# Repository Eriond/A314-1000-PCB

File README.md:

# A314-1000-PCB
A314 board for the A1000's front memory expansion bay

<p>This is the Amiga 1000 version of [the A314](https://github.com/niklasekstrom/a314), designed to fit in the front expansion bay of the iconic computer.<br>
It is built using readily available components and has been designed with the DIY builder in mind (ie. no BGA chips, and reasonably large components with external leads)</p>
<p>It is a 1:1 replacement for the A1050 C= memory expansion, and will provide 256kB of chipRAM regardless if the RPiZ module is present.<br>
The board has room for an optional RTC chip which can provide time and date to the RPiZ via an I2C bus. This bus has also been made available via solderpads and is accessible from both sides of the PCB. It can be useful if you'd like to add other peripherals, like RGB lights or an OLED display for instance.</p>

For more information on how to bring this hardware to life, please check out Niklas repository at [https://github.com/niklasekstrom/a314-1000-gateware](https://github.com/niklasekstrom/a314-1000-gateware)

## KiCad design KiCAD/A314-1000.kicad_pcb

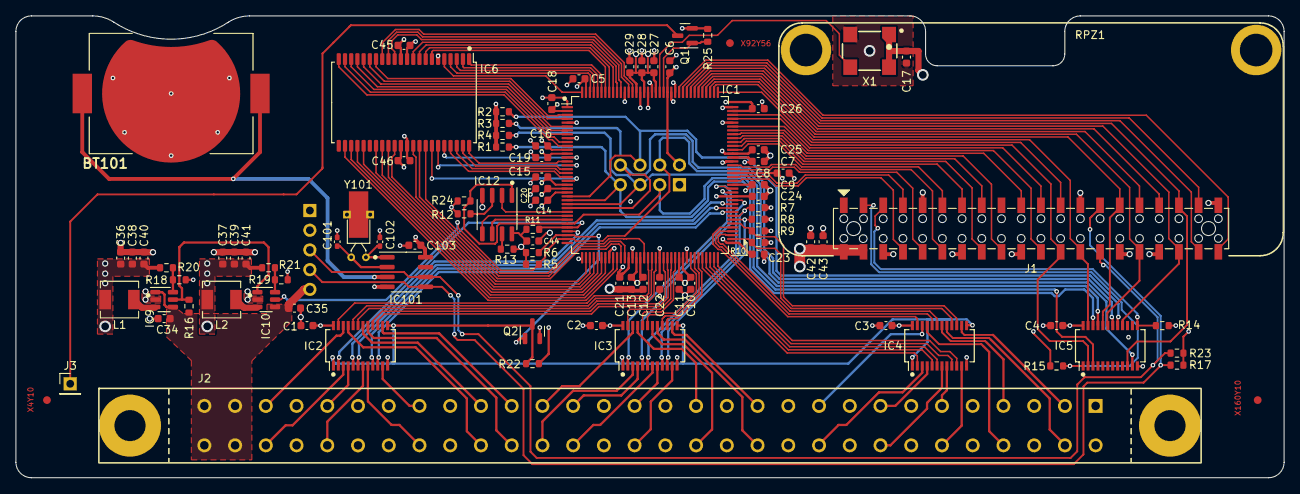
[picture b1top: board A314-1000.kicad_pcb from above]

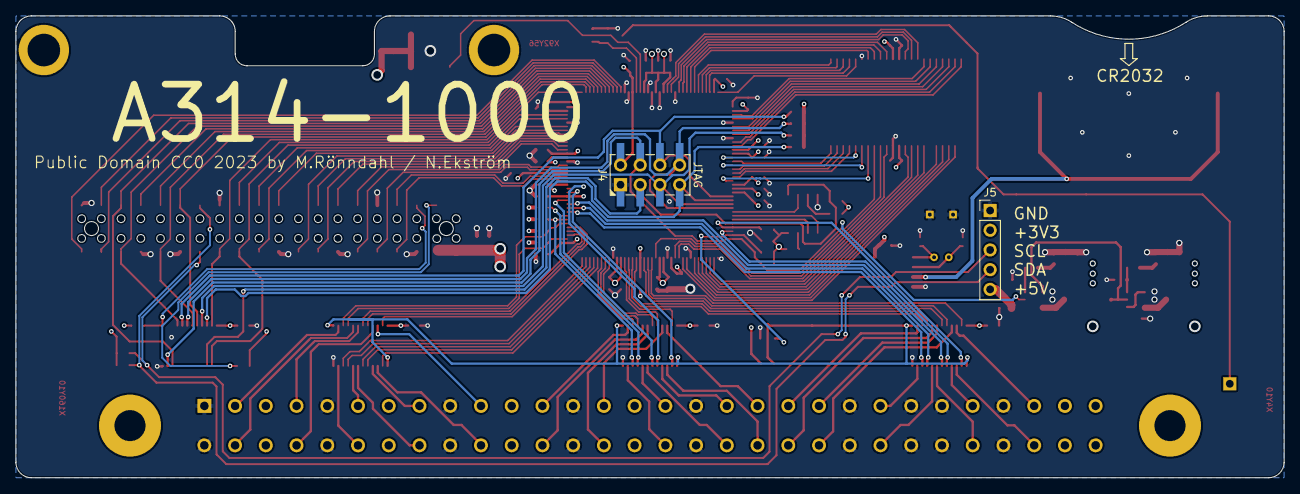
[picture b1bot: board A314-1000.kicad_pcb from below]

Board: 4 copper layers, 163.4 x 59.5 mm, 98 parts (2 on the bottom side), 153 nets.

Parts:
BT101: CR2032; BATHLD001
C1, C2, C3, C4, C5, C6, C7, C8, C9, C10, C11, C12, C13, C14, C15, C16, C17, C18, C19, C20, C21, C22, C23, C24, C25, C26, C27, C28, C29, C44, C45, C46, C103: 100n; C_0603_1608Metric
C34, C35: 4µ7; C_0603_1608Metric
C36, C37, C38, C39, C40, C41, C42, C43: 10µ; C_0603_1608Metric
C101, C102: 8p; C_0402_1005Metric_Pad0.74x0.62mm_HandSolder
FID1, FID2, FID3: Fiducial; Fiducial_1mm_Mask2mm
H1, H2: MountingHole; M2.5_Mount
IC1: T8Q144xx; LQFP-144_20x20mm_P0.5mm
IC2, IC3, IC4, IC5: SN74CBTD3384CPWR; SSOP-24_3.9x8.7mm_P0.635mm
IC6: IS61WV12816EDBLL-10TLI; TSOP-II-44_10.16x18.41mm_P0.8mm
IC9, IC10: TLV62569P; SOT-23-6
IC12: W25Q80DVSN; SOIC-8_3.9x4.9mm_P1.27mm
IC101: PT7C4311WEX; SOIC-8_3.9x4.9mm_P1.27mm
J1: Raspberry_Pi_2_3; LianSheng-FH-00339
J2: 2x30 Card edge conn.; 337-060-52x-804
J3: INT2; PinHeader_1x01_P2.54mm_Vertical
J4: JTAG; PinHeader_2x04_P2.54mm_Vertical_Multi
J5: RASP_I2C; PinHeader_1x05_P2.54mm_Vertical
L1, L2: 2.2uH; L_Sunlord_MWSA0402S
Q1, Q2: 2N7002; SOT-23
R1, R2, R3, R4, R5, R6, R7, R8, R9, R10, R11, R12, R13, R14, R15, R24: 10k; R_0603_1608Metric
R16, R21: 442k; R_0603_1608Metric
R17, R23, R25: 3k9; R_0603_1608Metric
R18, R19, R20: 100k; R_0603_1608Metric
R22: 1k8; R_0603_1608Metric
RPZ1: RPiZ; RPiZ mount
X1: 25MHz; HSO751S
Y101: 32.768kHz; Crystal_DS26_D2.0mm_L6.0mm_Horizontal_1EP_style2

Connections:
+1V2: C18.1, C19.1, C20.1, C21.1, C22.1, C23.1, C24.1, C25.1, C26.1, C27.1, C28.1, C29.1, C36.1, C38.1, C40.1, IC1.2 (VCCA_TL), IC1.13 (VCC), IC1.22 (VCC), IC1.49 (VCC), IC1.57 (VCC), IC1.73 (VCCA_BR), IC1.85 (VCC), IC1.96 (VCC), IC1.107 (VCCA_TR), IC1.125 (VCC), IC1.128 (VCC), IC1.130 (VCC), L1.2, R20.2
+3V3: C5.1, C6.1, C7.1, C8.1, C9.1, C10.1, C11.1, C12.1, C13.1, C14.1, C15.1, C16.1, C17.1, C37.1, C39.1, C41.1, C44.1, C45.1, C46.1, C103.1, IC1.12 (VCCIO1CD), IC1.21 (VCCIO1B), IC1.23 (VCCIO1A), IC1.51 (VCCIO4B), IC1.52 (VCCIO4B), IC1.62 (VCCIO4A), IC1.63 (VCCIO4A), IC1.88 (VCCIO3E), IC1.91 (VCCIO3D), IC1.95 (VCCIO3BC), IC1.122 (VCCIO3A), IC1.143 (VCCIO1E), IC6.11 (VDD), IC6.33 (VDD), IC12.8 (VCC), IC101.8 (V_{cc}), J4.2 (Vcc), J5.2, L2.2, R1.2, R2.2, R3.2, R4.2, R5.2, R6.2, R7.2, R8.2, R9.2, R10.2, R11.2, R12.1, R13.2, R14.2, R15.2, R17.2, R21.2, R22.2, R23.2, R24.2, X1.1 (OE), X1.4 (Vdd)
+5V: C1.1, C2.1, C3.1, C4.1, C34.1, C35.1, C42.1, C43.1, IC2.24 (VCC), IC3.24 (VCC), IC4.24 (VCC), IC5.24 (VCC), IC9.1 (EN), IC9.4 (VIN), IC10.4 (VIN), J1.2 (5V), J1.4 (5V), J2.3, J2.7, J2.11, J2.15, J2.29, J2.30, J2.C, J2.H, J2.HH, J2.JJ, J2.M, J2.S, J5.5, R16.2
/1V2PG: IC9.5 (PG), IC10.1 (EN), R16.1
/3VA_{0}: IC1.55 (GPIOB_RXP00), IC2.20 (2B4)
/3VA_{1}: IC1.58 (GPIOB_RXP02), IC2.16 (2B2)
/3VA_{2}: IC1.86 (GPIOR_133/CDI18), IC3.2 (1B1)
/3VA_{3}: IC1.84 (GPIOR_135/CDI17), IC3.6 (1B3)
/3VA_{4}: IC1.87 (GPIOR_132/CDI19), IC3.5 (1B2)
/3VA_{5}: IC1.60 (GPIOB_RXN03), IC3.23 (2B5)
/3VA_{6}: IC1.59 (GPIOB_RXN02), IC2.15 (2B1)
/3VA_{7}: IC1.56 (GPIOB_RXN00), IC2.19 (2B3)
/3VCASL_{0}: IC1.54 (GPIOB_TXN11), IC2.23 (2B5)
/3VCASL_{1}: IC1.32 (GPIOL_04/CSI), IC2.2 (1B1), R11.1
/3VCASU_{0}: IC1.33 (GPIOL_05/CSO), IC2.5 (1B2)
/3VCASU_{1}: IC1.83 (GPIOR_136/CDI16), IC2.6 (1B3)
/3VD_{0}: IC1.80 (GPIOR_149/CBUS2), IC3.9 (1B4), R7.1
/3VD_{1}: IC1.79 (GPIOR_150/CBUS1), IC3.10 (1B5), R8.1
/3VD_{2}: IC1.65 (GPIOB_RXN07), IC3.19 (2B3)
/3VD_{3}: IC1.61 (GPIOB_RXP03), IC3.20 (2B4)
/3VD_{4}: IC1.67 (GPIOB_RXP10), IC3.15 (2B1)
/3VD_{5}: IC1.66 (GPIOB_RXP07), IC3.16 (2B2)
/3VD_{6}: IC1.68 (GPIOB_RXN10), IC4.2 (1B1)
/3VD_{7}: IC1.77 (GPIOR_154), IC4.23 (2B5)
/3VD_{8}: IC1.69 (GPIOB_RXN12_EXTFB0), IC4.5 (1B2)
/3VD_{9}: IC1.70 (GPIOB_RXP12_EXTFB0), IC4.6 (1B3)
/3VD_{10}: IC1.72 (GPIOB_CLKN0), IC4.10 (1B5)
/3VD_{11}: IC1.71 (GPIOB_CLKP0), IC4.9 (1B4)
/3VD_{12}: IC1.75 (GPIOR_157/PLLIN), IC4.19 (2B3)
/3VD_{13}: IC1.76 (GPIOR_155), IC4.20 (2B4)
/3VD_{14}: IC1.74 (GPIOR_158/~TEST), IC4.16 (2B2), R10.1
/3VD_{15}: IC1.78 (GPIOR_151/CBUS0), IC4.15 (2B1), R9.1
/3VRAS: IC1.81 (GPIOR_139), IC2.10 (1B5)
/3VRRW: IC1.82 (GPIOR_138), IC2.9 (1B4)
/AMA_{0}: IC2.21 (2A4), J2.Y
/AMA_{1}: IC2.17 (2A2), J2.X
/AMA_{2}: IC3.3 (1A1), J2.W
/AMA_{3}: IC3.7 (1A3), J2.V
/AMA_{4}: IC3.4 (1A2), J2.18
/AMA_{5}: IC3.22 (2A5), J2.19
/AMA_{6}: IC2.14 (2A1), J2.20
/AMA_{7}: IC2.18 (2A3), J2.21
/AMCASL_{0}: IC2.22 (2A5), J2.28
/AMCASL_{1}: IC2.3 (1A1), J2.FF
/AMCASU_{0}: IC2.4 (1A2), J2.26
/AMCASU_{1}: IC2.7 (1A3), J2.DD
/AMD_{0}: IC3.8 (1A4), J2.16
/AMD_{1}: IC3.11 (1A5), J2.T
/AMD_{2}: IC3.18 (2A3), J2.R
/AMD_{3}: IC3.21 (2A4), J2.14
/AMD_{4}: IC3.14 (2A1), J2.12
/AMD_{5}: IC3.17 (2A2), J2.N
/AMD_{6}: IC4.3 (1A1), J2.L
/AMD_{7}: IC4.22 (2A5), J2.10
/AMD_{8}: IC4.4 (1A2), J2.8
/AMD_{9}: IC4.7 (1A3), J2.J
/AMD_{10}: IC4.11 (1A5), J2.F
/AMD_{11}: IC4.8 (1A4), J2.6
/AMD_{12}: IC4.18 (2A3), J2.4
/AMD_{13}: IC4.21 (2A4), J2.D
/AMD_{14}: IC4.17 (2A2), J2.B
/AMD_{15}: IC4.14 (2A1), J2.2
/AMRAS: IC2.11 (1A5), J2.23
/AMRRW: IC2.8 (1A4), J2.AA
/A_{0}: IC1.144 (GPIOL_64), IC6.5 (A0)
/A_{1}: IC1.142 (GPIOL_66/CDI12), IC6.4 (A1)
/A_{2}: IC1.141 (GPIOL_65), IC6.3 (A2)
/A_{3}: IC1.140 (GPIOL_67/CDI13), IC6.2 (A3)
/A_{4}: IC1.139 (GPIOL_68), IC6.1 (A4)
/A_{5}: IC1.15 (GPIOL_24_CLK0), IC6.44 (A5)
/A_{6}: IC1.17 (GPIOL_21_CTRL1_CDI5), IC6.43 (A6)
/A_{7}: IC1.18 (GPIOL_20_CTRL0_CDI4), IC6.42 (A7)
/A_{8}: IC1.42 (GPIOB_TXP04), IC6.27 (A8)
/A_{9}: IC1.43 (GPIOB_TXN04), IC6.26 (A9)
/A_{10}: IC1.45 (GPIOB_TXP06), IC6.25 (A10)
/A_{11}: IC1.46 (GPIOB_TXN06), IC6.24 (A11)
/A_{12}: IC1.11 (GPIOL_31_CLK7_CDI6), IC6.22 (A12)
/A_{13}: IC1.10 (GPIOL_32_CTRL4_CDI7), IC6.21 (A13)
/A_{14}: IC1.8 (GPIOL_40_CDI8), IC6.20 (A14)
/A_{15}: IC1.7 (GPIOL_41_CDI9), IC6.19 (A15)
/A_{16}: IC1.6 (GPIOL_46), IC6.18 (A16)
/DI: IC1.29 (GPIOL_08/CDI0), IC12.5 (DI)
/DO: IC1.28 (GPIOL_09/CDI1), IC12.2 (DO)
/DONE: IC1.34 (CDONE), Q2.1 (G), R6.1
/D_{0}: IC1.138 (GPIOL_69/CBSEL1), IC6.7 (D0)
/D_{1}: IC1.137 (GPIOL_70/CBSEL0), IC6.8 (D1)
/D_{2}: IC1.136 (GPIOL_71/NSTATUS), IC6.9 (D2)
/D_{3}: IC1.135 (GPIOL_72/ExtFB0/CDI14), IC6.10 (D3)
/D_{4}: IC1.134 (GPIOL_73/ExtFB1/CDI15), IC6.13 (D4)
/D_{5}: IC1.132 (GPIOL_74/PLLIN0), IC6.14 (D5)
/D_{6}: IC1.131 (GPIOL_75/PLLIN1), IC6.15 (D6)
/D_{7}: IC1.3 (GPIOL_53_CDI10), IC6.16 (D7)
/D_{8}: IC1.41 (GPIOB_TXN02), IC6.29 (D8)
/D_{9}: IC1.40 (GPIOB_TXP02), IC6.30 (D9)
/D_{10}: IC1.39 (GPIOB_TXN00), IC6.31 (D10)
/D_{11}: IC1.38 (GPIOB_TXP00), IC6.32 (D11)
/D_{12}: IC1.47 (GPIOB_TXP09), IC6.35 (D12)
/D_{13}: IC1.48 (GPIOB_TXN09), IC6.36 (D13)
/D_{14}: IC1.53 (GPIOB_TXP11), IC6.37 (D14)
/D_{15}: IC1.20 (GPIOL_12_CDI2), IC6.38 (D15)
/FRCLK: IC1.30 (GPIOL_01/CCK), IC12.6 (CLK)
/JTAG_OE_{0}: IC5.13 (2~OE), J1.5 (SCL/GPIO3), R14.1
/JTAG_OE_{1}: IC5.1 (1~OE), J1.3 (SDA/GPIO2), R15.1
/PIACK: IC1.100 (GPIOR_113/CDI22), J1.15 (GPIO22)
/PIA_{0}: IC1.101 (GPIOR_112/CDI23), J1.18 (GPIO24)
/PIA_{1}: IC1.103 (GPIOR_104/CDI25), J1.22 (GPIO25)
/PIA_{2}: IC1.118 (GPIOR_79/ExtFB1/CDI30), J1.37 (GPIO26)
/PIA_{3}: IC1.98 (GPIOR_117/CTRL14), J1.13 (GPIO27)
/PID_{0}: IC1.90 (GPIOR_128/CTRL11), J1.7 (GCLK0/GPIO4)
/PID_{1}: IC1.111 (GPIOR_85), IC5.20 (2B4), J1.29 (GCLK1/GPIO5)
/PID_{2}: IC1.113 (GPIOR_84), J1.31 (GCLK2/GPIO6)
/PID_{3}: IC1.110 (GPIOR_87/CDI29), IC5.23 (2B5), J1.26 (~CE1/GPIO7)
/PID_{4}: IC1.106 (GPIOR_94/CDI27), IC5.2 (1B1), J1.24 (~CE0/GPIO8)
/PID_{5}: IC1.105 (GPIOR_95/CDI26), J1.21 (MISO0/GPIO9)
/PID_{6}: IC1.102 (GPIOR_105/CDI24), J1.19 (MOSI0/GPIO10)
/PID_{7}: IC1.109 (GPIOR_88/CDI28), J1.23 (SCLK0/GPIO11)
/PID_{8}: IC1.112 (GPIOR_86), IC5.19 (2B3), J1.32 (PWM0/GPIO12)
/PID_{9}: IC1.114 (GPIOR_83), J1.33 (PWM1/GPIO13)
/PID_{10}: IC1.89 (GPIOR_129/CTRL10), J1.8 (GPIO14/TXD)
/PID_{11}: IC1.92 (GPIOR_125/CLK10), J1.10 (GPIO15/RXD)
/PID_{12}: IC1.115 (GPIOR_82), IC5.16 (2B2), J1.36 (GPIO16)
/PID_{13}: IC1.97 (GPIOR_122/CLK13/CDI21), J1.11 (GPIO17)
/PID_{14}: IC1.93 (GPIOR_123/CLK12/CDI20), J1.12 (GPIO18/PWM0)
/PID_{15}: IC1.116 (GPIOR_81/MrefCLK), IC5.10 (1B5), J1.35 (GPIO19/MISO1)
/PIIRQ: IC1.99 (GPIOR_116/CTRL15), J1.16 (GPIO23)
/PIREQ: IC1.119 (GPIOR_78/ExtFB0/CDI31), J1.40 (GPIO21/SCLK1)
/PIWR: IC1.117 (GPIOR_80), J1.38 (GPIO20/MOSI1)
/SCL: IC101.6 (SCL), J1.28 (ID_SC/GPIO1), J5.3, R23.1
/SDA: IC101.5 (SDA), J1.27 (ID_SD/GPIO0), J5.4, R17.1
/SPI_SS: IC1.31 (GPIOL_00/~SS), IC5.3 (1A1), IC12.1 (~CS), J4.3 (~SPI_SS), R24.1
/TCK: IC1.26 (TCK), IC5.21 (2A4), J4.5 (TCK), R4.1
/TDI: IC1.27 (TDI), IC5.18 (2A3), J4.8 (TDI), R3.1
/TDO: IC1.24 (TDO), IC5.17 (2A2), J4.6 (TDO), R2.1
/TMS: IC1.25 (TMS), IC5.22 (2A5), J4.7 (TMS), R1.1
/~CRESET: IC1.35 (~CRESET), IC5.11 (1A5), IC10.5 (PG), J4.4 (~CRESET), R5.1
/~DONE: IC2.1 (1~OE), IC2.13 (2~OE), IC3.1 (1~OE), IC3.13 (2~OE), IC4.1 (1~OE), IC4.13 (2~OE), Q2.3 (D), R22.1
/~LB: IC1.16 (GPIOL_22_CTRL2), IC6.39 (~LB)
/~OE: IC1.19 (GPIOL_13_CDI3), IC6.41 (~OE)
/~UB: IC1.14 (GPIOL_25_CLK1), IC6.40 (~UB)
/~WE: IC1.4 (GPIOL_54_CDI11), IC6.17 (~WE)
GND: BT101.2 (-), C1.2, C2.2, C3.2, C4.2, C5.2, C6.2, C7.2, C8.2, C9.2, C10.2, C11.2, C12.2, C13.2, C14.2, C15.2, C16.2, C17.2, C18.2, C19.2, C20.2, C21.2, C22.2, C23.2, C24.2, C25.2, C26.2, C27.2, C28.2, C29.2, C34.2, C35.2, C36.2, C37.2, C38.2, C39.2, C40.2, C41.2, C42.2, C43.2, C44.2, C45.2, C46.2, C101.2, C102.2, C103.2, IC1.1 (GND), IC1.5 (GND), IC1.9 (GND), IC1.37 (GND), IC1.44 (GND), IC1.50 (GND), IC1.64 (GND), IC1.94 (GND), IC1.104 (GND), IC1.108 (GND), IC1.120 (GND), IC1.121 (GND), IC1.126 (GND), IC1.127 (GND), IC1.129 (GND), IC1.133 (GND), IC2.12 (GND), IC3.12 (GND), IC4.12 (GND), IC5.12 (GND), IC6.6 (~CE), IC6.12 (GND), IC6.34 (GND), IC9.2 (GND), IC10.2 (GND), IC12.4 (GND), IC101.4 (GND), J1.6 (GND), J1.9 (GND), J1.14 (GND), J1.20 (GND), J1.25 (GND), J1.30 (GND), J1.34 (GND), J1.39 (GND), J2.1, J2.5 (Pin_55), J2.9, J2.13, J2.17, J2.22, J2.24, J2.25, J2.27, J2.A, J2.BB, J2.CC, J2.E, J2.EE, J2.K, J2.P, J2.U, J2.Z, J4.1 (GND), J5.1, Q1.2 (S), Q2.2 (S), R18.1, R19.1, R25.1, X1.2 (GND), Y101.3
unnamed: BT101.1 (+), IC101.3 (V_{bat})
unnamed: IC1.124 (GPIOR_76/PLLIN0), X1.3 (OUT)
unnamed: IC1.123 (GPIOR_77/PLLIN1), Q1.1 (G), R25.2
unnamed: IC9.6 (FB), R18.2, R20.1
unnamed: IC9.3 (SW), L1.1
unnamed: IC10.6 (FB), R19.2, R21.1
unnamed: IC10.3 (SW), L2.1
unnamed: IC12.7 (~HOLD), R13.1
unnamed: IC12.3 (~WP), R12.2
unnamed: C102.1, IC101.1 (X1), Y101.1
unnamed: C101.1, IC101.2 (X2), Y101.2
unnamed: J3.1, Q1.3 (D)

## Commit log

2023-04-30 Initial commit
    Work in Progress. Only for review, not complete.
2023-05-01 Ready for production?
    Board finished, added a RTC for the RPi. With a little luck and some production files, this may be ready for some PCBA :)
2023-05-03 Simplified PSU
    Enhanced battery replacement ergonomics
2023-05-03 Updated PCB image
2023-05-04 General cleanup
    Removed irrelevant files, addressed a number of DRC issues and cleaned up a footprint or two :)
2023-06-11 First bug-ridded release
    This is the first non-alpha release. The hardware issues that were found in the alpha have been addressed. This board is now sent for a second production run.
2023-08-23 Real-world images
2023-08-23 Update README.md
    Changed the render for a real-world image
2023-09-20 Update README.md
    The board is now in a mature, production-proven state. This update removes previous alpha- and beta-related comments.

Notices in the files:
KiCAD/A314-1000.kicad_pcb:
Public Domain CC0 2023 by M.Rönndahl / N.Ekström
